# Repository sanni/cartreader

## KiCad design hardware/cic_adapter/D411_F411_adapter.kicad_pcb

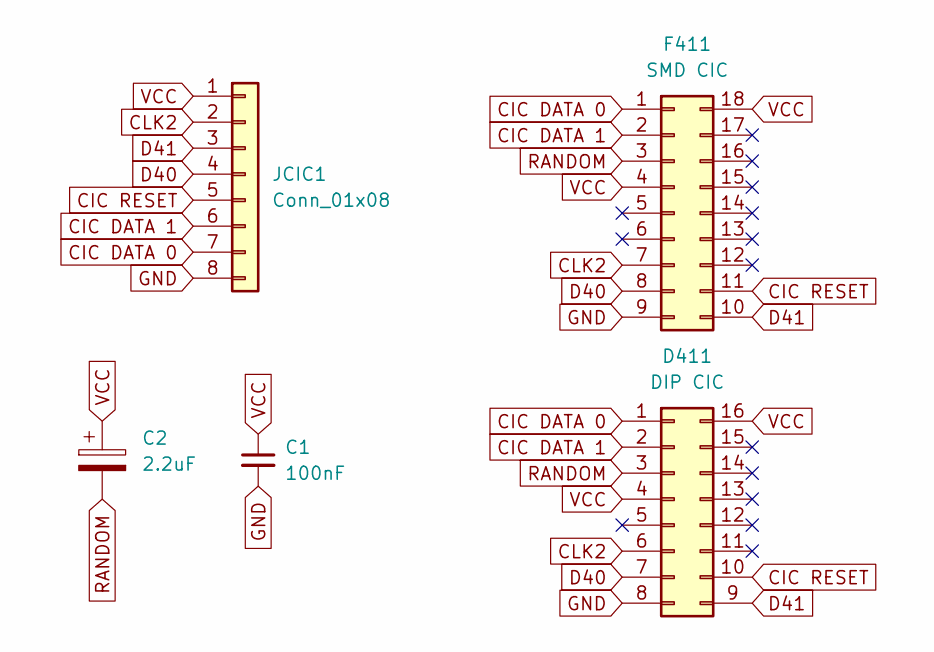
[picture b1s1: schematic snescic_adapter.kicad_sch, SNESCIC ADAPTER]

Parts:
C1: 100nF
C2: 2.2uF
D411: DIP CIC
F411: SMD CIC
JCIC1: Conn_01x08

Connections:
CIC DATA 0: D411.1, F411.1, JCIC1.7
CIC DATA 1: D411.2, F411.2, JCIC1.6
CIC RESET: D411.10, F411.11, JCIC1.5
CLK2: D411.6, F411.7, JCIC1.2
D40: D411.7, F411.8, JCIC1.4
D41: D411.9, F411.10, JCIC1.3
GND: C1.2, D411.8, F411.9, JCIC1.8
RANDOM: C2.2, D411.3, F411.3
VCC: C1.1, C2.1, D411.4, D411.16, F411.4, F411.18, JCIC1.1

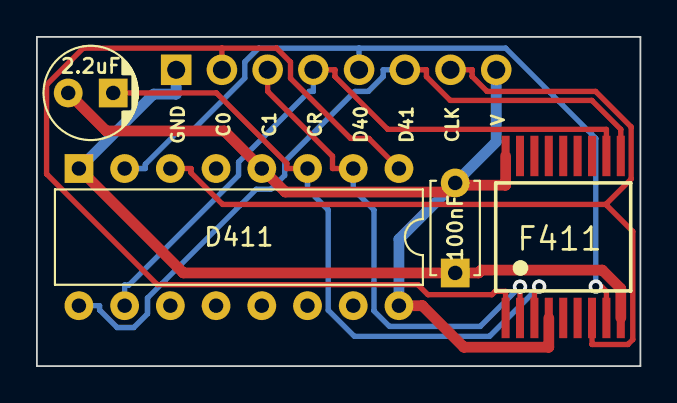
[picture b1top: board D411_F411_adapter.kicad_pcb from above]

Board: 2 copper layers, 33.5 x 18.3 mm, 5 parts (1 on the bottom side), 9 nets.

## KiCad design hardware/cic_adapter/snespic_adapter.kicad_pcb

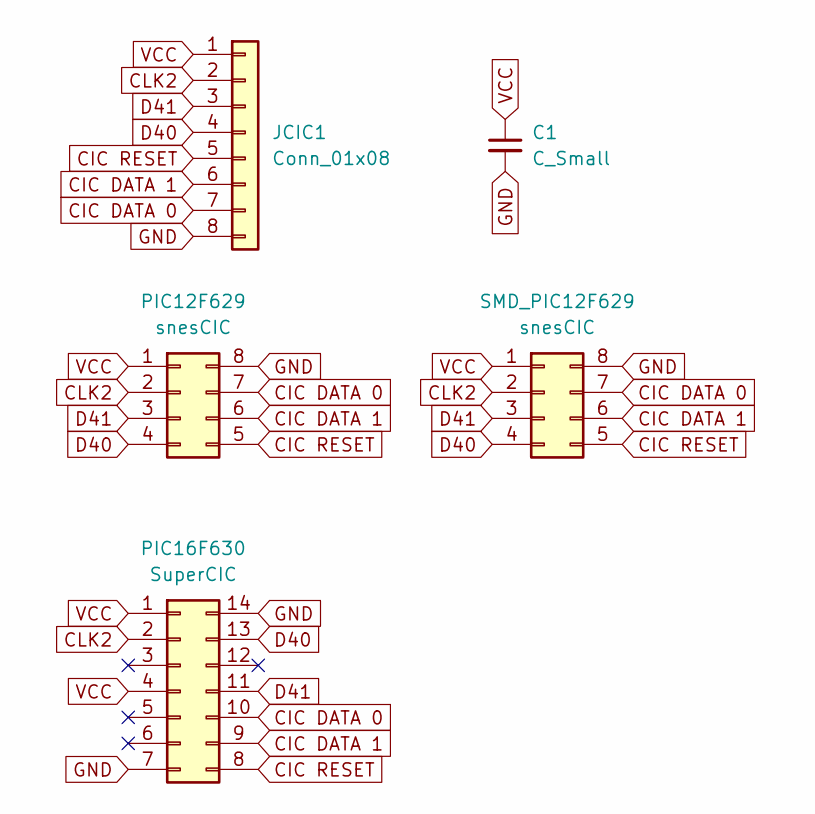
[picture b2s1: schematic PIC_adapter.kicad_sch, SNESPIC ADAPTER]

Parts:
C1: C_Small
JCIC1: Conn_01x08
PIC12F629: snesCIC
PIC16F630: SuperCIC
SMD_PIC12F629: snesCIC

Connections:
CIC DATA 0: JCIC1.7, PIC12F629.7, PIC16F630.10, SMD_PIC12F629.7
CIC DATA 1: JCIC1.6, PIC12F629.6, PIC16F630.9, SMD_PIC12F629.6
CIC RESET: JCIC1.5, PIC12F629.5, PIC16F630.8, SMD_PIC12F629.5
CLK2: JCIC1.2, PIC12F629.2, PIC16F630.2, SMD_PIC12F629.2
D40: JCIC1.4, PIC12F629.4, PIC16F630.13, SMD_PIC12F629.4
D41: JCIC1.3, PIC12F629.3, PIC16F630.11, SMD_PIC12F629.3
GND: C1.2, JCIC1.8, PIC12F629.8, PIC16F630.7, PIC16F630.14, SMD_PIC12F629.8
VCC: C1.1, JCIC1.1, PIC12F629.1, PIC16F630.1, PIC16F630.4, SMD_PIC12F629.1

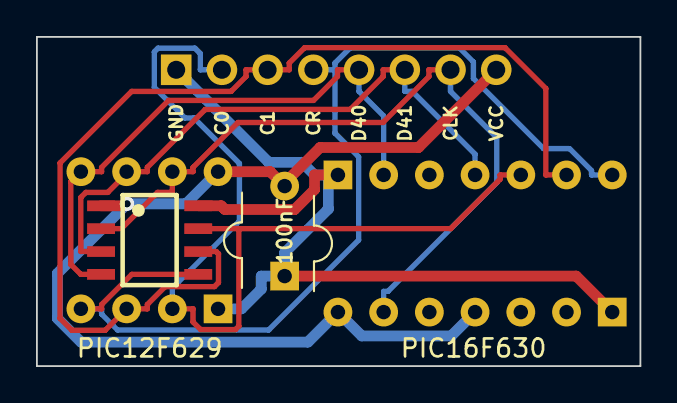
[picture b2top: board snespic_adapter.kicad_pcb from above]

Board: 2 copper layers, 33.5 x 18.3 mm, 5 parts (1 on the bottom side), 8 nets.

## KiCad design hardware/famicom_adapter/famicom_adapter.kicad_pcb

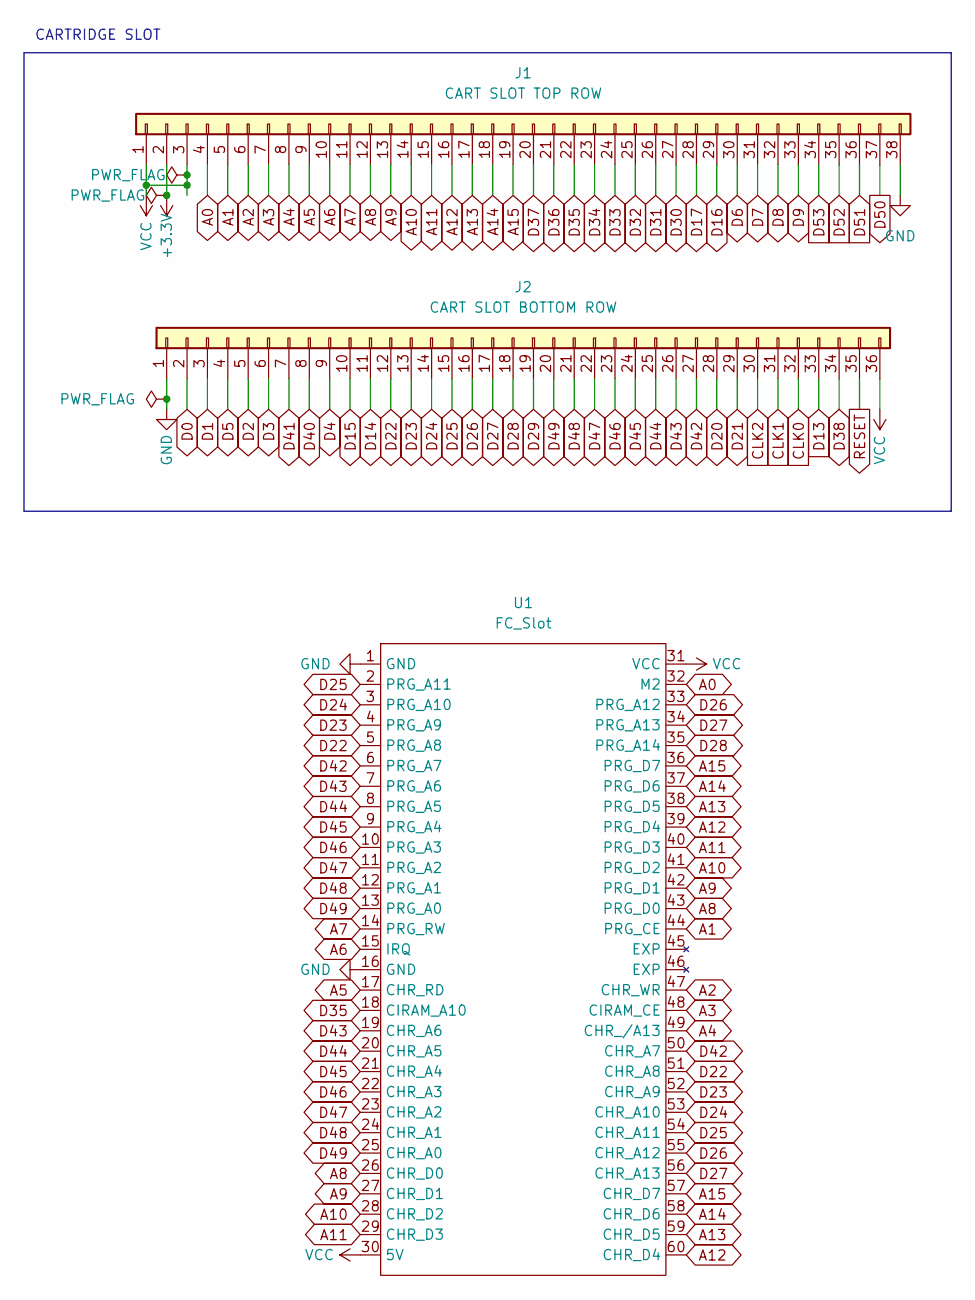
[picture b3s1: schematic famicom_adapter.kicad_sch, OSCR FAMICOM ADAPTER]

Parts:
J1: CART SLOT TOP ROW; PinSocket_1x38_P2.54mm_Vertical
J2: CART SLOT BOTTOM ROW; PinSocket_1x36_P2.54mm_Vertical
U1: FC_Slot

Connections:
+3V3: J1.2
A0: J1.4, U1.32 (M2)
A1: J1.5, U1.44 (PRG_CE)
A2: J1.6, U1.47 (CHR_WR)
A3: J1.7, U1.48 (CIRAM_CE)
A4: J1.8, U1.49 (CHR_/A13)
A5: J1.9, U1.17 (CHR_RD)
A6: J1.10, U1.15 (IRQ)
A7: J1.11, U1.14 (PRG_RW)
A8: J1.12, U1.26 (CHR_D0), U1.43 (PRG_D0)
A9: J1.13, U1.27 (CHR_D1), U1.42 (PRG_D1)
A10: J1.14, U1.28 (CHR_D2), U1.41 (PRG_D2)
A11: J1.15, U1.29 (CHR_D3), U1.40 (PRG_D3)
A12: J1.16, U1.39 (PRG_D4), U1.60 (CHR_D4)
A13: J1.17, U1.38 (PRG_D5), U1.59 (CHR_D5)
A14: J1.18, U1.37 (PRG_D6), U1.58 (CHR_D6)
A15: J1.19, U1.36 (PRG_D7), U1.57 (CHR_D7)
CLK0: J2.32
CLK1: J2.31
CLK2: J2.30
D0: J2.2
D1: J2.3
D2: J2.5
D3: J2.6
D4: J2.9
D5: J2.4
D6: J1.30
D7: J1.31
D8: J1.32
D9: J1.33
D13: J2.33
D14: J2.11
D15: J2.10
D16: J1.29
D17: J1.28
D20: J2.28
D21: J2.29
D22: J2.12, U1.5 (PRG_A8), U1.51 (CHR_A8)
D23: J2.13, U1.4 (PRG_A9), U1.52 (CHR_A9)
D24: J2.14, U1.3 (PRG_A10), U1.53 (CHR_A10)
D25: J2.15, U1.2 (PRG_A11), U1.54 (CHR_A11)
D26: J2.16, U1.33 (PRG_A12), U1.55 (CHR_A12)
D27: J2.17, U1.34 (PRG_A13), U1.56 (CHR_A13)
D28: J2.18, U1.35 (PRG_A14)
D29: J2.19
D30: J1.27
D31: J1.26
D32: J1.25
D33: J1.24
D34: J1.23
D35: J1.22, U1.18 (CIRAM_A10)
D36: J1.21
D37: J1.20
D38: J2.34
D40: J2.8
D41: J2.7
D42: J2.27, U1.6 (PRG_A7), U1.50 (CHR_A7)
D43: J2.26, U1.7 (PRG_A6), U1.19 (CHR_A6)
D44: J2.25, U1.8 (PRG_A5), U1.20 (CHR_A5)
D45: J2.24, U1.9 (PRG_A4), U1.21 (CHR_A4)
D46: J2.23, U1.10 (PRG_A3), U1.22 (CHR_A3)
D47: J2.22, U1.11 (PRG_A2), U1.23 (CHR_A2)
D48: J2.21, U1.12 (PRG_A1), U1.24 (CHR_A1)
D49: J2.20, U1.13 (PRG_A0), U1.25 (CHR_A0)
D50: J1.37
D51: J1.36
D52: J1.35
D53: J1.34
GND: J1.38, J2.1, U1.1 (GND), U1.16 (GND)
RESET: J2.35
VCC: J1.1, J1.3, J2.36, U1.30 (5V), U1.31 (VCC)

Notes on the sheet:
CARTRIDGE SLOT

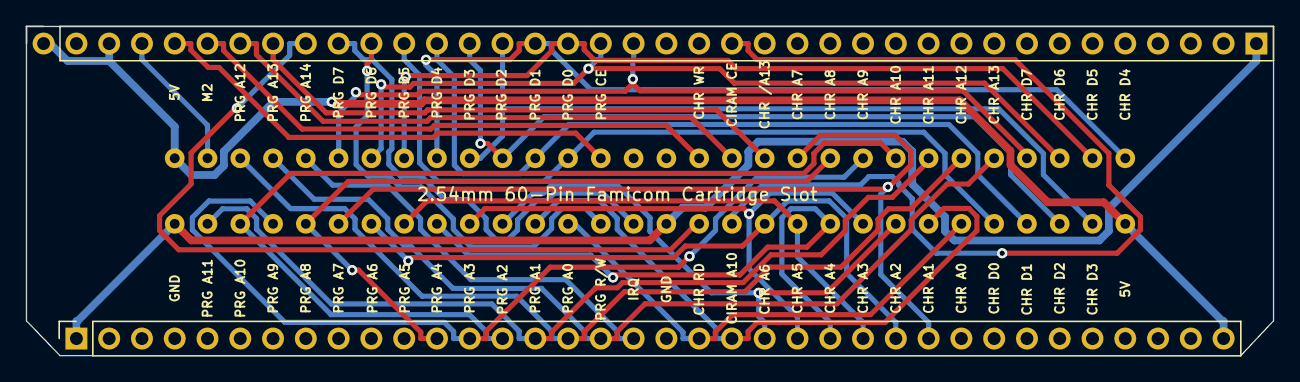
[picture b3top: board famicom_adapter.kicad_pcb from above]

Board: 2 copper layers, 96.6 x 25.5 mm, 3 parts (0 on the bottom side), 34 nets.

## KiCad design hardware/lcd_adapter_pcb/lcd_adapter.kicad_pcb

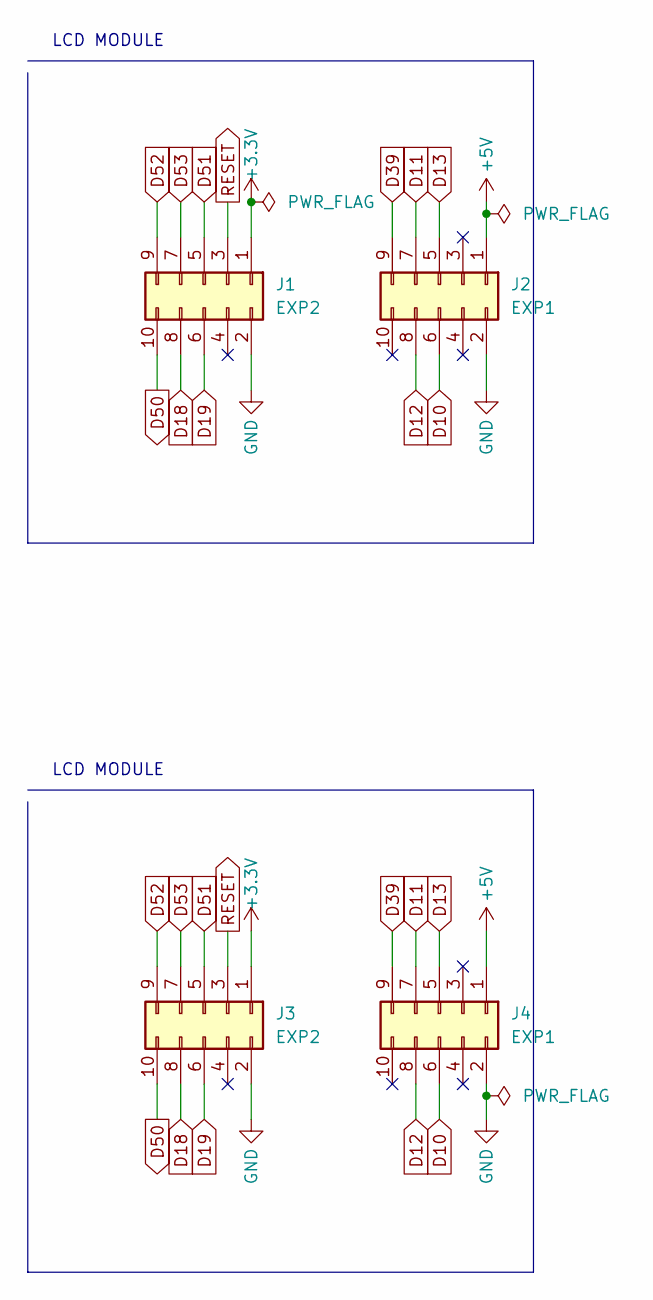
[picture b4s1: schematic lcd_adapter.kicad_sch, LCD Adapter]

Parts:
J1, J3: EXP2; IDC-Header_2x05_P2.54mm_Vertical
J2, J4: EXP1; IDC-Header_2x05_P2.54mm_Vertical

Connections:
+3V3: J1.1, J3.1
+5V: J2.1, J4.1
D10: J2.6, J4.6
D11: J2.7, J4.7
D12: J2.8, J4.8
D13: J2.5, J4.5
D18: J1.8, J3.8
D19: J1.6, J3.6
D39: J2.9, J4.9
D50: J1.10, J3.10
D51: J1.5, J3.5
D52: J1.9, J3.9
D53: J1.7, J3.7
GND: J1.2, J2.2, J3.2, J4.2
RESET: J1.3, J3.3

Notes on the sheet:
LCD MODULE

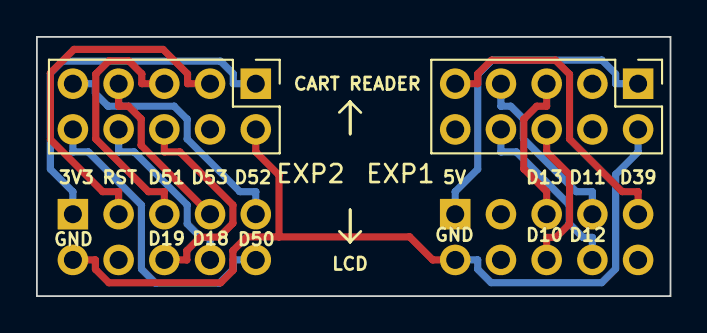
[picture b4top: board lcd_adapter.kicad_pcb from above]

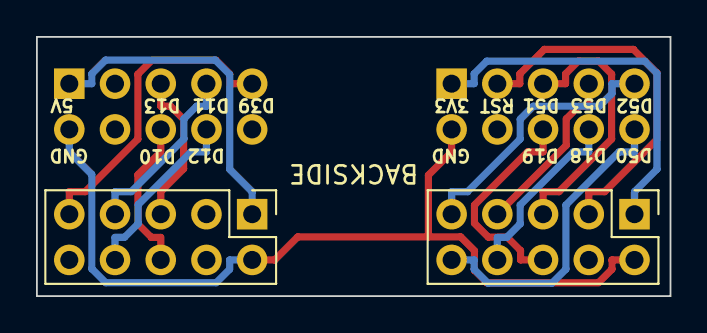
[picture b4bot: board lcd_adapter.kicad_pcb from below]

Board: 2 copper layers, 35.2 x 14.4 mm, 4 parts (2 on the bottom side), 15 nets.

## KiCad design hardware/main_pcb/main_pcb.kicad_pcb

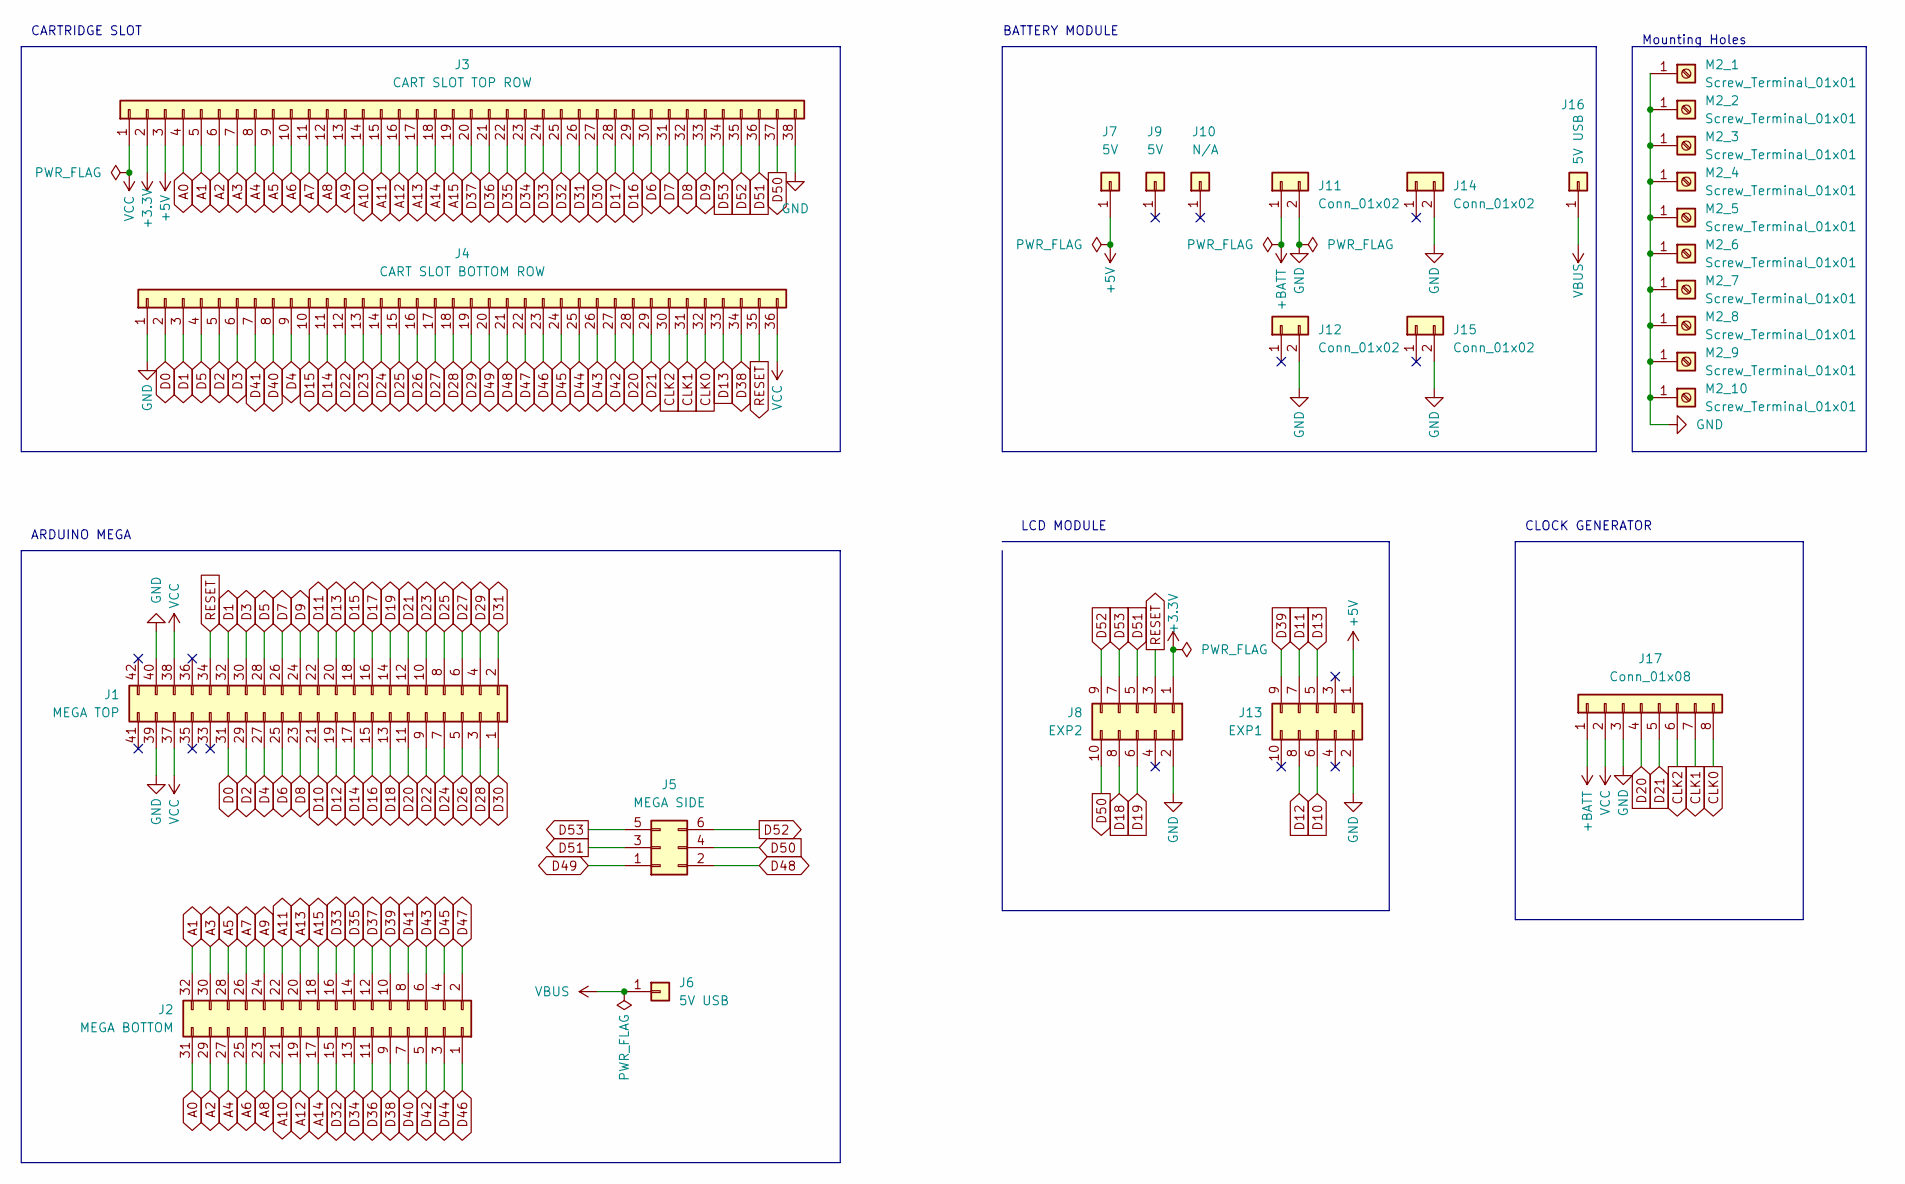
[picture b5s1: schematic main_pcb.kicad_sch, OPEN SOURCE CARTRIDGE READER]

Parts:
J1: MEGA TOP; PinSocket_2x21_P2.54mm_Vertical
J2: MEGA BOTTOM; PinSocket_2x16_P2.54mm_Vertical
J3: CART SLOT TOP ROW; PinSocket_1x38_P2.54mm_Vertical
J4: CART SLOT BOTTOM ROW; PinSocket_1x36_P2.54mm_Vertical
J5: MEGA SIDE; PinSocket_2x03_P2.54mm_Vertical
J6, J16: 5V USB; PinHeader_1x01_P2.54mm_Vertical
J7, J9: 5V; PinHeader_1x01_P2.54mm_Vertical
J8: EXP2; IDC-Header_2x05_P2.54mm_Vertical
J10: N/A; PinHeader_1x01_P2.54mm_Vertical
J11, J12, J14, J15: Conn_01x02; PinHeader_1x02_P2.54mm_Vertical
J13: EXP1; IDC-Header_2x05_P2.54mm_Vertical
J17: Conn_01x08; PinSocket_1x08_P2.54mm_Vertical
M2_1, M2_2, M2_3, M2_4, M2_5, M2_6, M2_7, M2_8, M2_9, M2_10: Screw_Terminal_01x01

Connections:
+3V3: J3.2, J8.1
+5V: J3.3, J7.1, J13.1
+BATT: J11.1, J17.1
A0: J2.31, J3.4
A1: J2.32, J3.5
A2: J2.29, J3.6
A3: J2.30, J3.7
A4: J2.27, J3.8
A5: J2.28, J3.9
A6: J2.25, J3.10
A7: J2.26, J3.11
A8: J2.23, J3.12
A9: J2.24, J3.13
A10: J2.21, J3.14
A11: J2.22, J3.15
A12: J2.19, J3.16
A13: J2.20, J3.17
A14: J2.17, J3.18
A15: J2.18, J3.19
CLK0: J4.32, J17.8
CLK1: J4.31, J17.7
CLK2: J4.30, J17.6
D0: J1.31, J4.2
D1: J1.32, J4.3
D2: J1.29, J4.5
D3: J1.30, J4.6
D4: J1.27, J4.9
D5: J1.28, J4.4
D6: J1.25, J3.30
D7: J1.26, J3.31
D8: J1.23, J3.32
D9: J1.24, J3.33
D10: J1.21, J13.6
D11: J1.22, J13.7
D12: J1.19, J13.8
D13: J1.20, J4.33, J13.5
D14: J1.17, J4.11
D15: J1.18, J4.10
D16: J1.15, J3.29
D17: J1.16, J3.28
D18: J1.13, J8.8
D19: J1.14, J8.6
D20: J1.11, J4.28, J17.4
D21: J1.12, J4.29, J17.5
D22: J1.9, J4.12
D23: J1.10, J4.13
D24: J1.7, J4.14
D25: J1.8, J4.15
D26: J1.5, J4.16
D27: J1.6, J4.17
D28: J1.3, J4.18
D29: J1.4, J4.19
D30: J1.1, J3.27
D31: J1.2, J3.26
D32: J2.15, J3.25
D33: J2.16, J3.24
D34: J2.13, J3.23
D35: J2.14, J3.22
D36: J2.11, J3.21
D37: J2.12, J3.20
D38: J2.9, J4.34
D39: J2.10, J13.9
D40: J2.7, J4.8
D41: J2.8, J4.7
D42: J2.5, J4.27
D43: J2.6, J4.26
D44: J2.3, J4.25
D45: J2.4, J4.24
D46: J2.1, J4.23
D47: J2.2, J4.22
D48: J4.21, J5.2
D49: J4.20, J5.1
D50: J3.37, J5.4, J8.10
D51: J3.36, J5.3, J8.5
D52: J3.35, J5.6, J8.9
D53: J3.34, J5.5, J8.7
GND: J1.39, J1.40, J3.38, J4.1, J8.2, J11.2, J12.2, J13.2, J14.2, J15.2, J17.3, M2_1.1, M2_2.1, M2_3.1, M2_4.1, M2_5.1, M2_6.1, M2_7.1, M2_8.1, M2_9.1, M2_10.1
RESET: J1.34, J4.35, J8.3
VBUS: J6.1, J16.1
VCC: J1.37, J1.38, J3.1, J4.36, J17.2

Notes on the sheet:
CARTRIDGE SLOT
ARDUINO MEGA
BATTERY MODULE
LCD MODULE
CLOCK GENERATOR
Mounting Holes

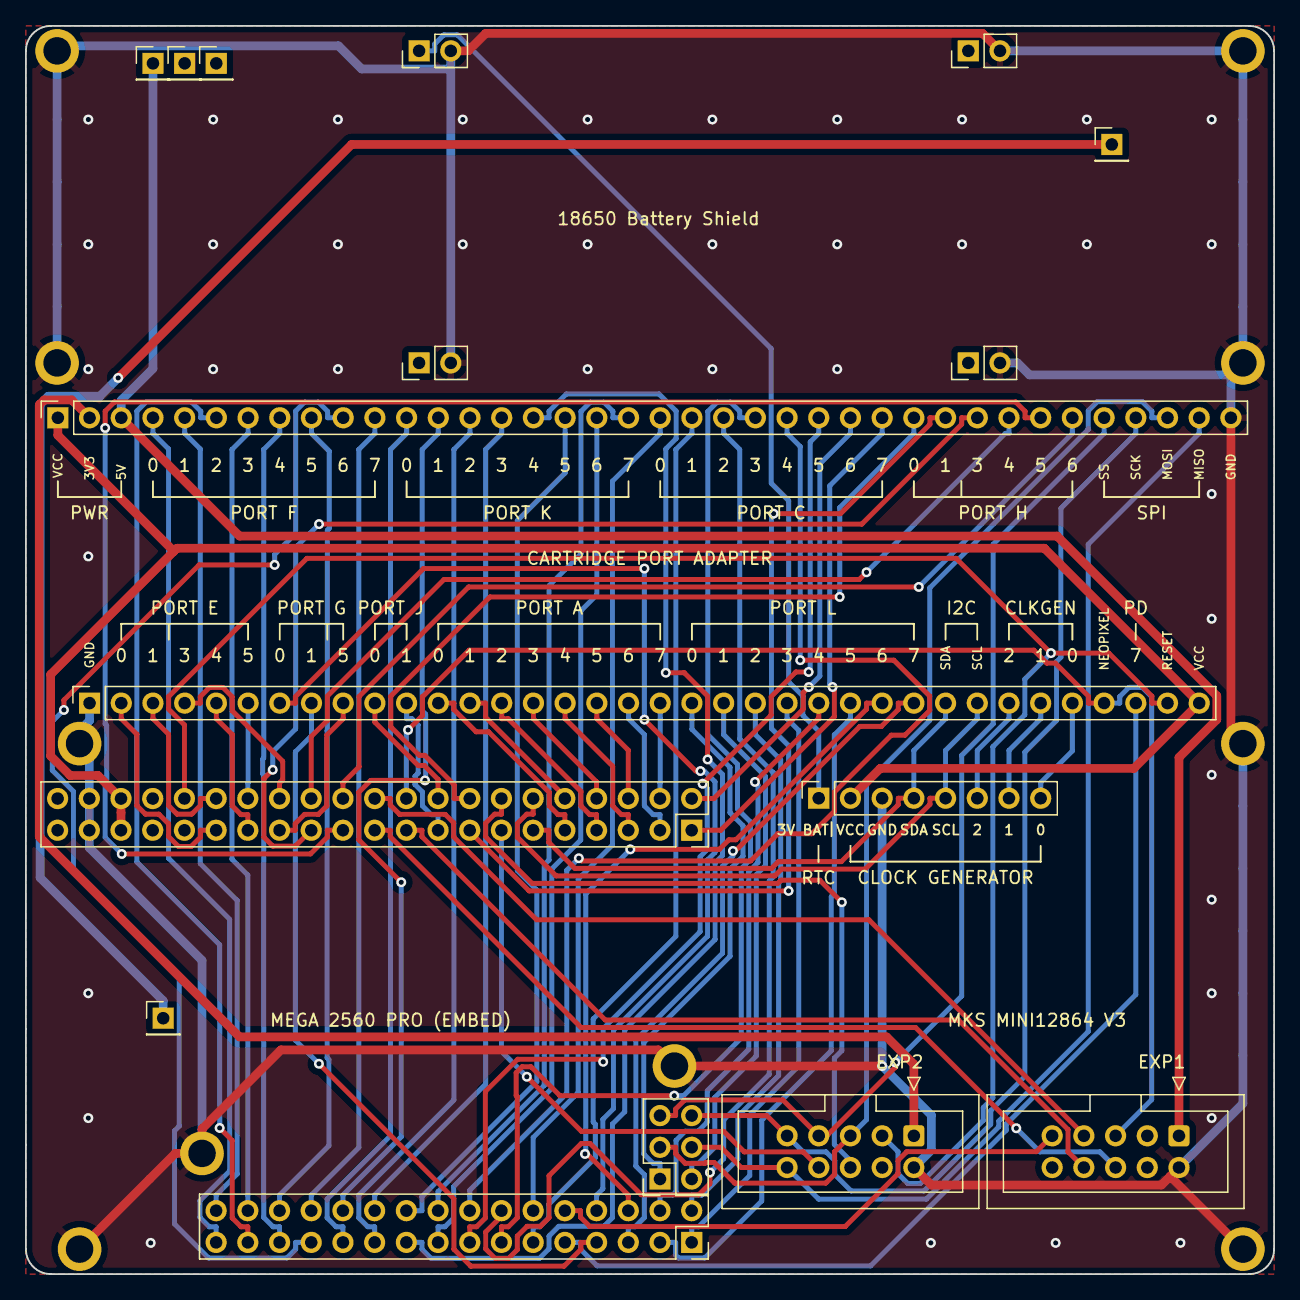
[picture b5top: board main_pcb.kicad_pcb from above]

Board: 2 copper layers, 100.0 x 100.0 mm, 27 parts (0 on the bottom side), 80 nets.

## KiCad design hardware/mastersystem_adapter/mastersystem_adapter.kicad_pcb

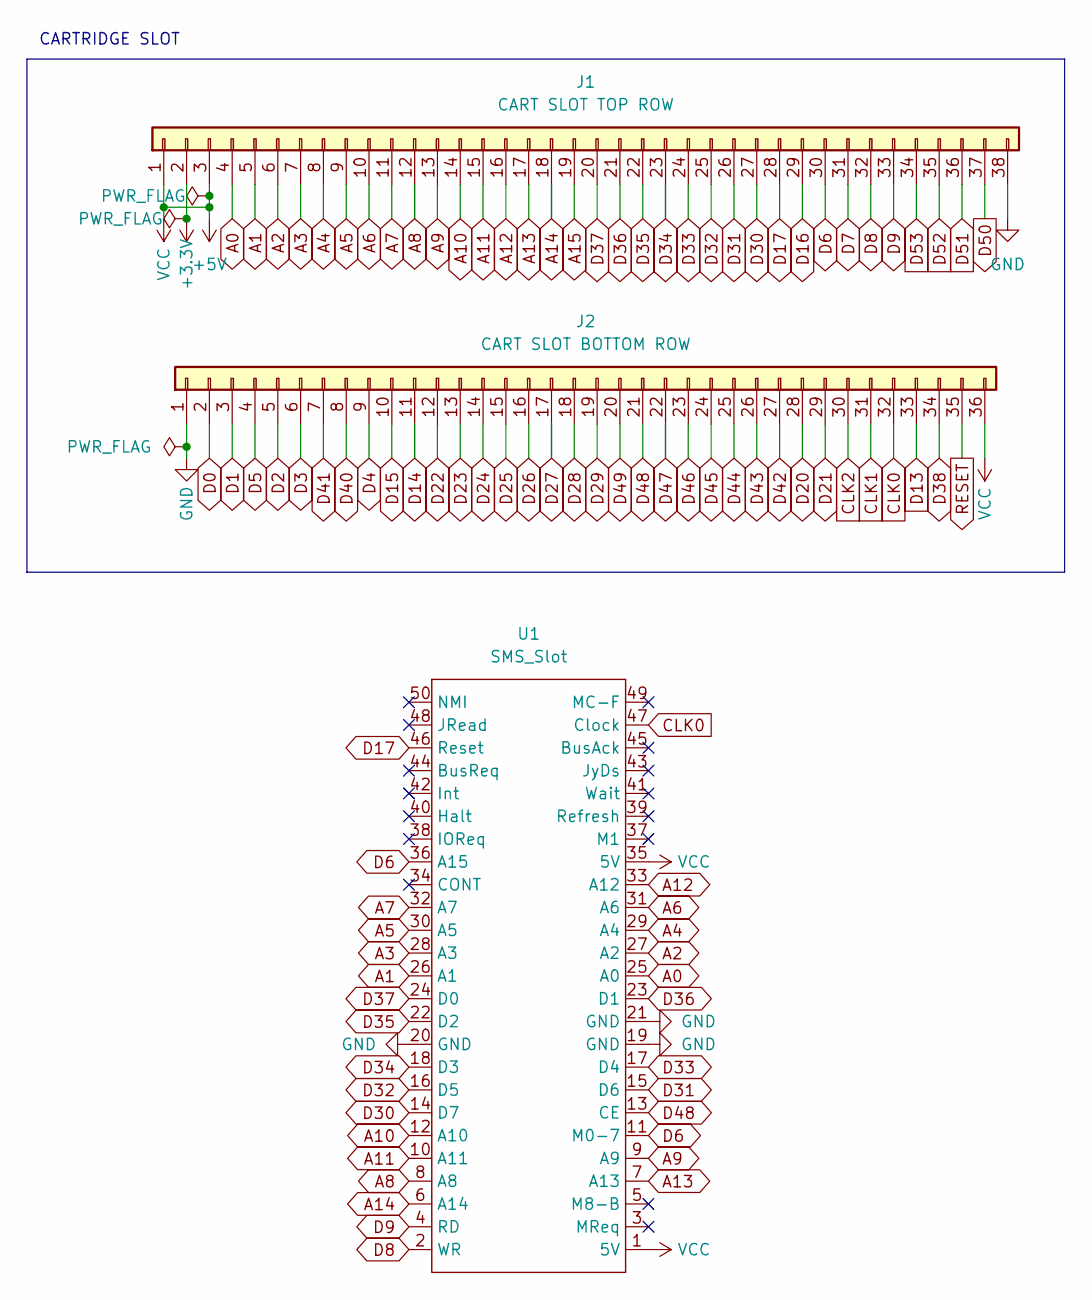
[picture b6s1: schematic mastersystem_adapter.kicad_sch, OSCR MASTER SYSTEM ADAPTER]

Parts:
J1: CART SLOT TOP ROW; PinSocket_1x38_P2.54mm_Vertical
J2: CART SLOT BOTTOM ROW; PinSocket_1x36_P2.54mm_Vertical
U1: SMS_Slot

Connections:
+3V3: J1.2
+5V: J1.1, J1.3, J2.36, U1.1 (5V), U1.35 (5V)
A0: J1.4, U1.25 (A0)
A1: J1.5, U1.26 (A1)
A2: J1.6, U1.27 (A2)
A3: J1.7, U1.28 (A3)
A4: J1.8, U1.29 (A4)
A5: J1.9, U1.30 (A5)
A6: J1.10, U1.31 (A6)
A7: J1.11, U1.32 (A7)
A8: J1.12, U1.8 (A8)
A9: J1.13, U1.9 (A9)
A10: J1.14, U1.12 (A10)
A11: J1.15, U1.10 (A11)
A12: J1.16, U1.33 (A12)
A13: J1.17, U1.7 (A13)
A14: J1.18, U1.6 (A14)
A15: J1.19
CLK0: J2.32, U1.47 (Clock)
CLK1: J2.31
CLK2: J2.30
D0: J2.2
D1: J2.3
D2: J2.5
D3: J2.6
D4: J2.9
D5: J2.4
D6: J1.30, U1.11 (M0-7), U1.36 (A15)
D7: J1.31
D8: J1.32, U1.2 (WR)
D9: J1.33, U1.4 (RD)
D13: J2.33
D14: J2.11
D15: J2.10
D16: J1.29
D17: J1.28, U1.46 (Reset)
D20: J2.28
D21: J2.29
D22: J2.12
D23: J2.13
D24: J2.14
D25: J2.15
D26: J2.16
D27: J2.17
D28: J2.18
D29: J2.19
D30: J1.27, U1.14 (D7)
D31: J1.26, U1.15 (D6)
D32: J1.25, U1.16 (D5)
D33: J1.24, U1.17 (D4)
D34: J1.23, U1.18 (D3)
D35: J1.22, U1.22 (D2)
D36: J1.21, U1.23 (D1)
D37: J1.20, U1.24 (D0)
D38: J2.34
D40: J2.8
D41: J2.7
D42: J2.27
D43: J2.26
D44: J2.25
D45: J2.24
D46: J2.23
D47: J2.22
D48: J2.21, U1.13 (CE)
D49: J2.20
D50: J1.37
D51: J1.36
D52: J1.35
D53: J1.34
GND: J1.38, J2.1, U1.19 (GND), U1.20 (GND), U1.21 (GND)
RESET: J2.35

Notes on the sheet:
CARTRIDGE SLOT

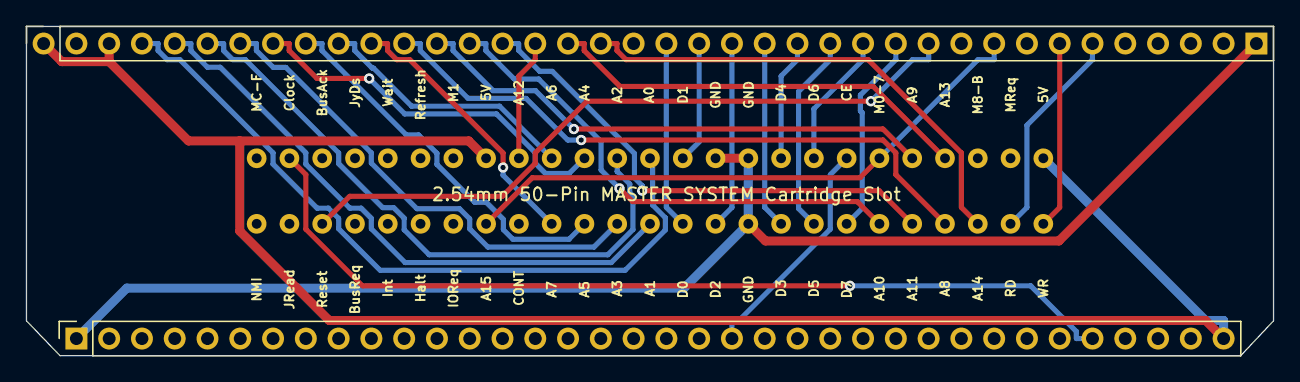
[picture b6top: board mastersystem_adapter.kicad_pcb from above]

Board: 2 copper layers, 96.6 x 25.5 mm, 3 parts (0 on the bottom side), 31 nets.

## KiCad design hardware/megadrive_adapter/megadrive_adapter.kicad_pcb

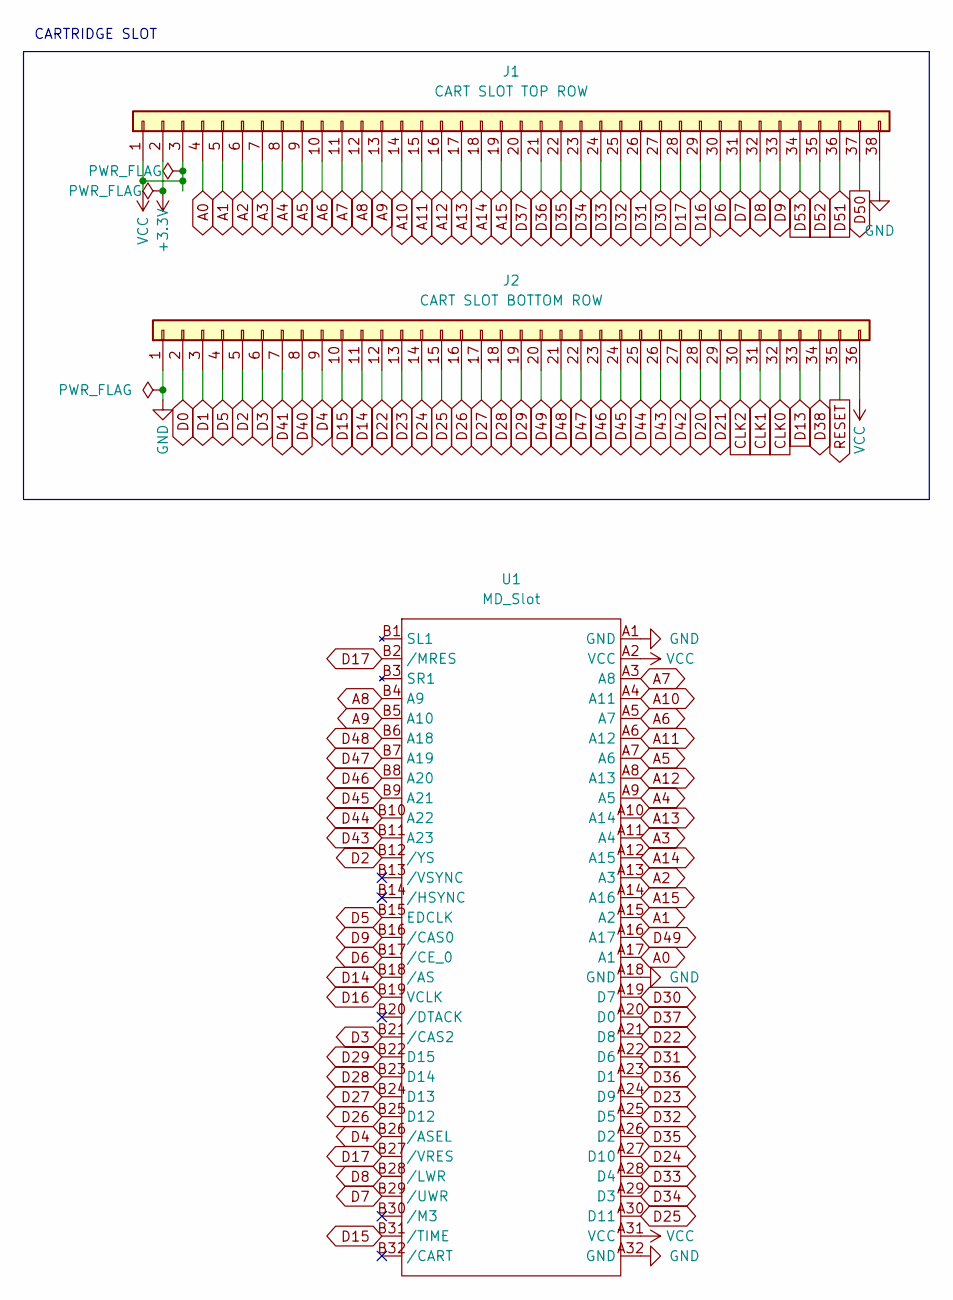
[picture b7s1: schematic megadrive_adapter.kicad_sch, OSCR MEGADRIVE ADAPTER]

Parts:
J1: CART SLOT TOP ROW; PinSocket_1x38_P2.54mm_Vertical
J2: CART SLOT BOTTOM ROW; PinSocket_1x36_P2.54mm_Vertical
U1: MD_Slot

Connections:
+3V3: J1.2
A0: J1.4, U1.A17 (A1)
A1: J1.5, U1.A15 (A2)
A2: J1.6, U1.A13 (A3)
A3: J1.7, U1.A11 (A4)
A4: J1.8, U1.A9 (A5)
A5: J1.9, U1.A7 (A6)
A6: J1.10, U1.A5 (A7)
A7: J1.11, U1.A3 (A8)
A8: J1.12, U1.B4 (A9)
A9: J1.13, U1.B5 (A10)
A10: J1.14, U1.A4 (A11)
A11: J1.15, U1.A6 (A12)
A12: J1.16, U1.A8 (A13)
A13: J1.17, U1.A10 (A14)
A14: J1.18, U1.A12 (A15)
A15: J1.19, U1.A14 (A16)
CLK0: J2.32
CLK1: J2.31
CLK2: J2.30
D0: J2.2
D1: J2.3
D2: J2.5, U1.B12 (/YS)
D3: J2.6, U1.B21 (/CAS2)
D4: J2.9, U1.B26 (/ASEL)
D5: J2.4, U1.B15 (EDCLK)
D6: J1.30, U1.B17 (/CE_0)
D7: J1.31, U1.B29 (/UWR)
D8: J1.32, U1.B28 (/LWR)
D9: J1.33, U1.B16 (/CAS0)
D13: J2.33
D14: J2.11, U1.B18 (/AS)
D15: J2.10, U1.B31 (/TIME)
D16: J1.29, U1.B19 (VCLK)
D17: J1.28, U1.B2 (/MRES), U1.B27 (/VRES)
D20: J2.28
D21: J2.29
D22: J2.12, U1.A21 (D8)
D23: J2.13, U1.A24 (D9)
D24: J2.14, U1.A27 (D10)
D25: J2.15, U1.A30 (D11)
D26: J2.16, U1.B25 (D12)
D27: J2.17, U1.B24 (D13)
D28: J2.18, U1.B23 (D14)
D29: J2.19, U1.B22 (D15)
D30: J1.27, U1.A19 (D7)
D31: J1.26, U1.A22 (D6)
D32: J1.25, U1.A25 (D5)
D33: J1.24, U1.A28 (D4)
D34: J1.23, U1.A29 (D3)
D35: J1.22, U1.A26 (D2)
D36: J1.21, U1.A23 (D1)
D37: J1.20, U1.A20 (D0)
D38: J2.34
D40: J2.8
D41: J2.7
D42: J2.27
D43: J2.26, U1.B11 (A23)
D44: J2.25, U1.B10 (A22)
D45: J2.24, U1.B9 (A21)
D46: J2.23, U1.B8 (A20)
D47: J2.22, U1.B7 (A19)
D48: J2.21, U1.B6 (A18)
D49: J2.20, U1.A16 (A17)
D50: J1.37
D51: J1.36
D52: J1.35
D53: J1.34
GND: J1.38, J2.1, U1.A1 (GND), U1.A18 (GND), U1.A32 (GND)
RESET: J2.35
VCC: J1.1, J1.3, J2.36, U1.A2 (VCC), U1.A31 (VCC)

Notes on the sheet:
CARTRIDGE SLOT

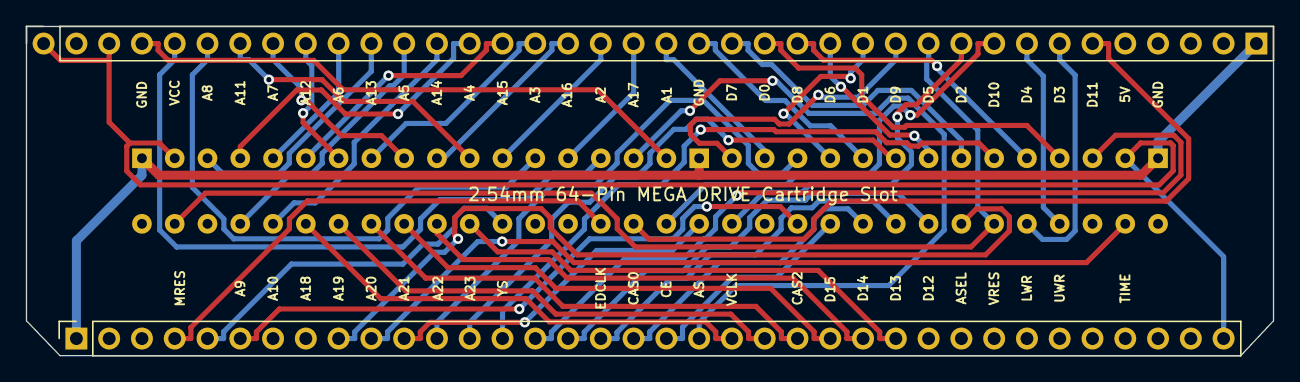
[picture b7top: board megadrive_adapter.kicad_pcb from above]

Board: 2 copper layers, 96.6 x 25.5 mm, 3 parts (0 on the bottom side), 53 nets.

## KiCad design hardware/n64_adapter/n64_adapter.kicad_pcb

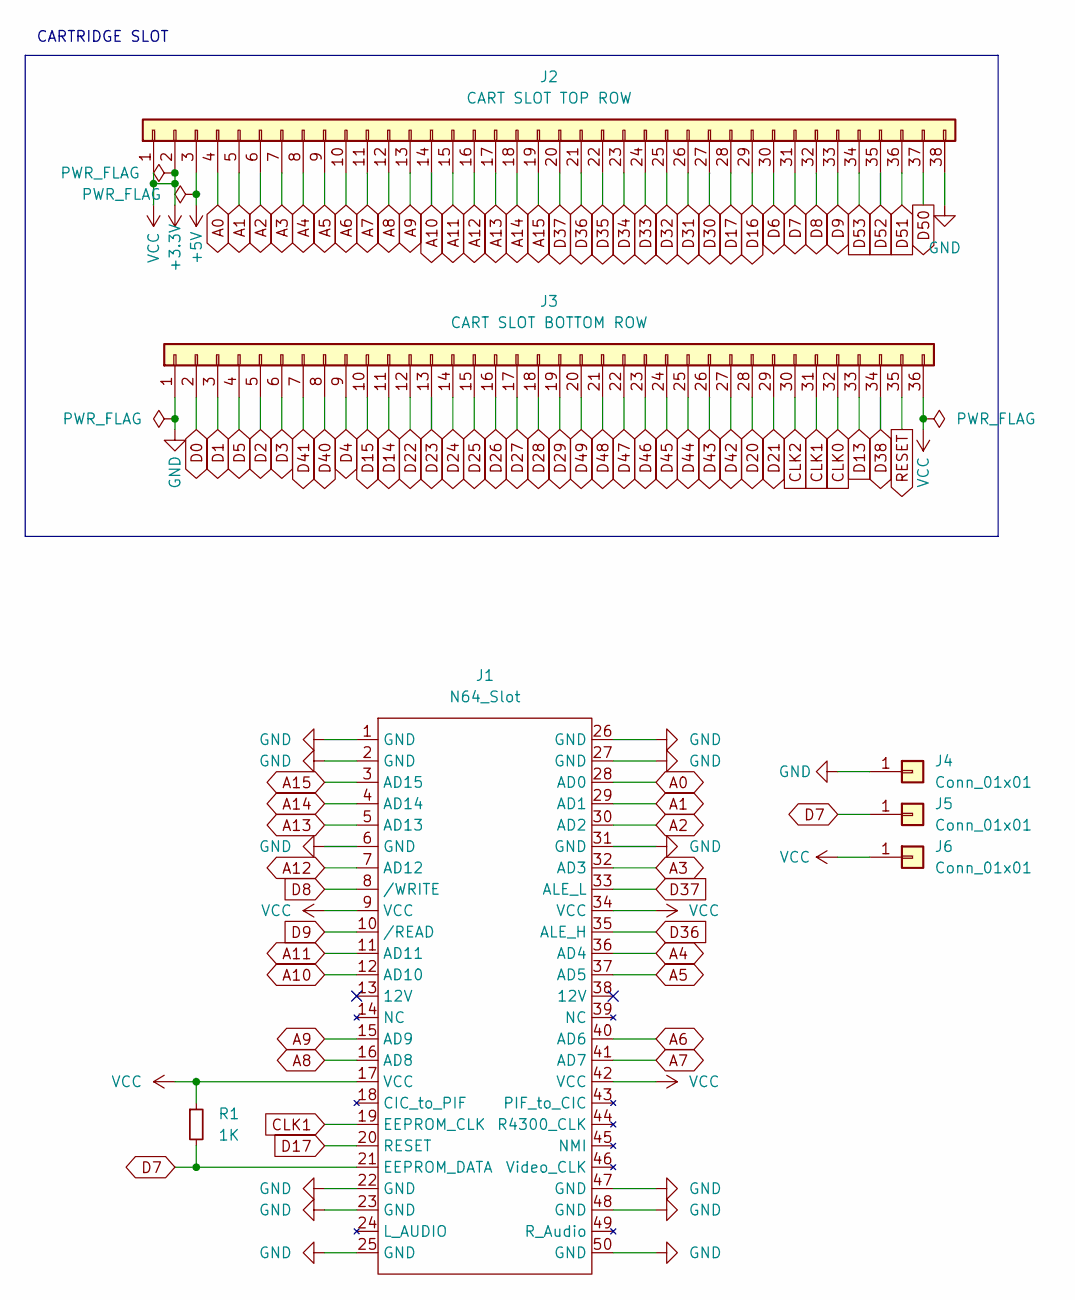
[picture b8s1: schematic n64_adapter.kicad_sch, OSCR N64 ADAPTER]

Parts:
J1: N64_Slot
J2: CART SLOT TOP ROW; PinSocket_1x38_P2.54mm_Vertical
J3: CART SLOT BOTTOM ROW; PinSocket_1x36_P2.54mm_Vertical
J4, J5, J6: Conn_01x01
R1: 1K

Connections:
+5V: J2.3
A0: J1.28 (AD0), J2.4
A1: J1.29 (AD1), J2.5
A2: J1.30 (AD2), J2.6
A3: J1.32 (AD3), J2.7
A4: J1.36 (AD4), J2.8
A5: J1.37 (AD5), J2.9
A6: J1.40 (AD6), J2.10
A7: J1.41 (AD7), J2.11
A8: J1.16 (AD8), J2.12
A9: J1.15 (AD9), J2.13
A10: J1.12 (AD10), J2.14
A11: J1.11 (AD11), J2.15
A12: J1.7 (AD12), J2.16
A13: J1.5 (AD13), J2.17
A14: J1.4 (AD14), J2.18
A15: J1.3 (AD15), J2.19
CLK0: J3.32
CLK1: J1.19 (EEPROM_CLK), J3.31
CLK2: J3.30
D0: J3.2
D1: J3.3
D2: J3.5
D3: J3.6
D4: J3.9
D5: J3.4
D6: J2.30
D7: J1.21 (EEPROM_DATA), J2.31, J5.1, R1.2
D8: J1.8 (/WRITE), J2.32
D9: J1.10 (/READ), J2.33
D13: J3.33
D14: J3.11
D15: J3.10
D16: J2.29
D17: J1.20 (RESET), J2.28
D20: J3.28
D21: J3.29
D22: J3.12
D23: J3.13
D24: J3.14
D25: J3.15
D26: J3.16
D27: J3.17
D28: J3.18
D29: J3.19
D30: J2.27
D31: J2.26
D32: J2.25
D33: J2.24
D34: J2.23
D35: J2.22
D36: J1.35 (ALE_H), J2.21
D37: J1.33 (ALE_L), J2.20
D38: J3.34
D40: J3.8
D41: J3.7
D42: J3.27
D43: J3.26
D44: J3.25
D45: J3.24
D46: J3.23
D47: J3.22
D48: J3.21
D49: J3.20
D50: J2.37
D51: J2.36
D52: J2.35
D53: J2.34
GND: J1.1 (GND), J1.2 (GND), J1.6 (GND), J1.22 (GND), J1.23 (GND), J1.25 (GND), J1.26 (GND), J1.27 (GND), J1.31 (GND), J1.47 (GND), J1.48 (GND), J1.50 (GND), J2.38, J3.1, J4.1
RESET: J3.35
VCC: J1.9 (VCC), J1.17 (VCC), J1.34 (VCC), J1.42 (VCC), J2.1, J2.2, J3.36, J6.1, R1.1

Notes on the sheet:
CARTRIDGE SLOT

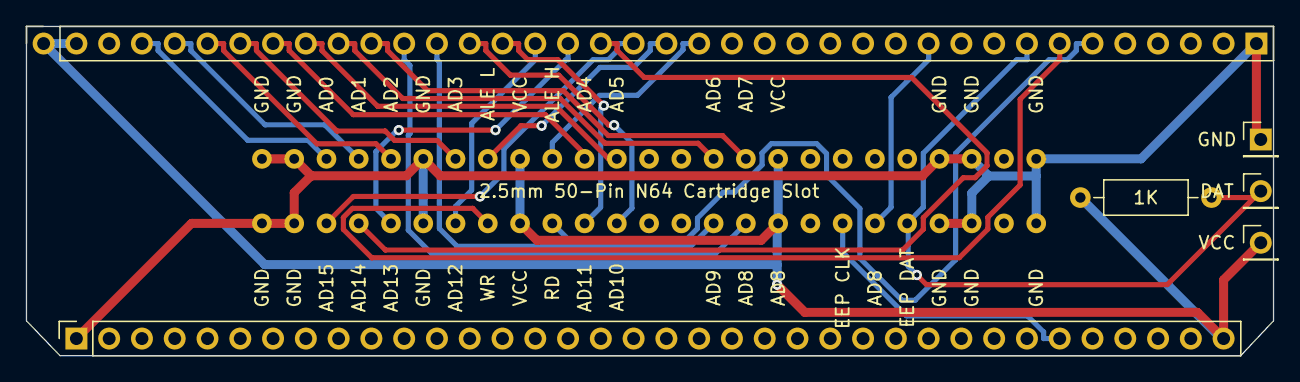
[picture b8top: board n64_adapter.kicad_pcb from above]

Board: 2 copper layers, 96.6 x 25.5 mm, 7 parts (0 on the bottom side), 25 nets.
